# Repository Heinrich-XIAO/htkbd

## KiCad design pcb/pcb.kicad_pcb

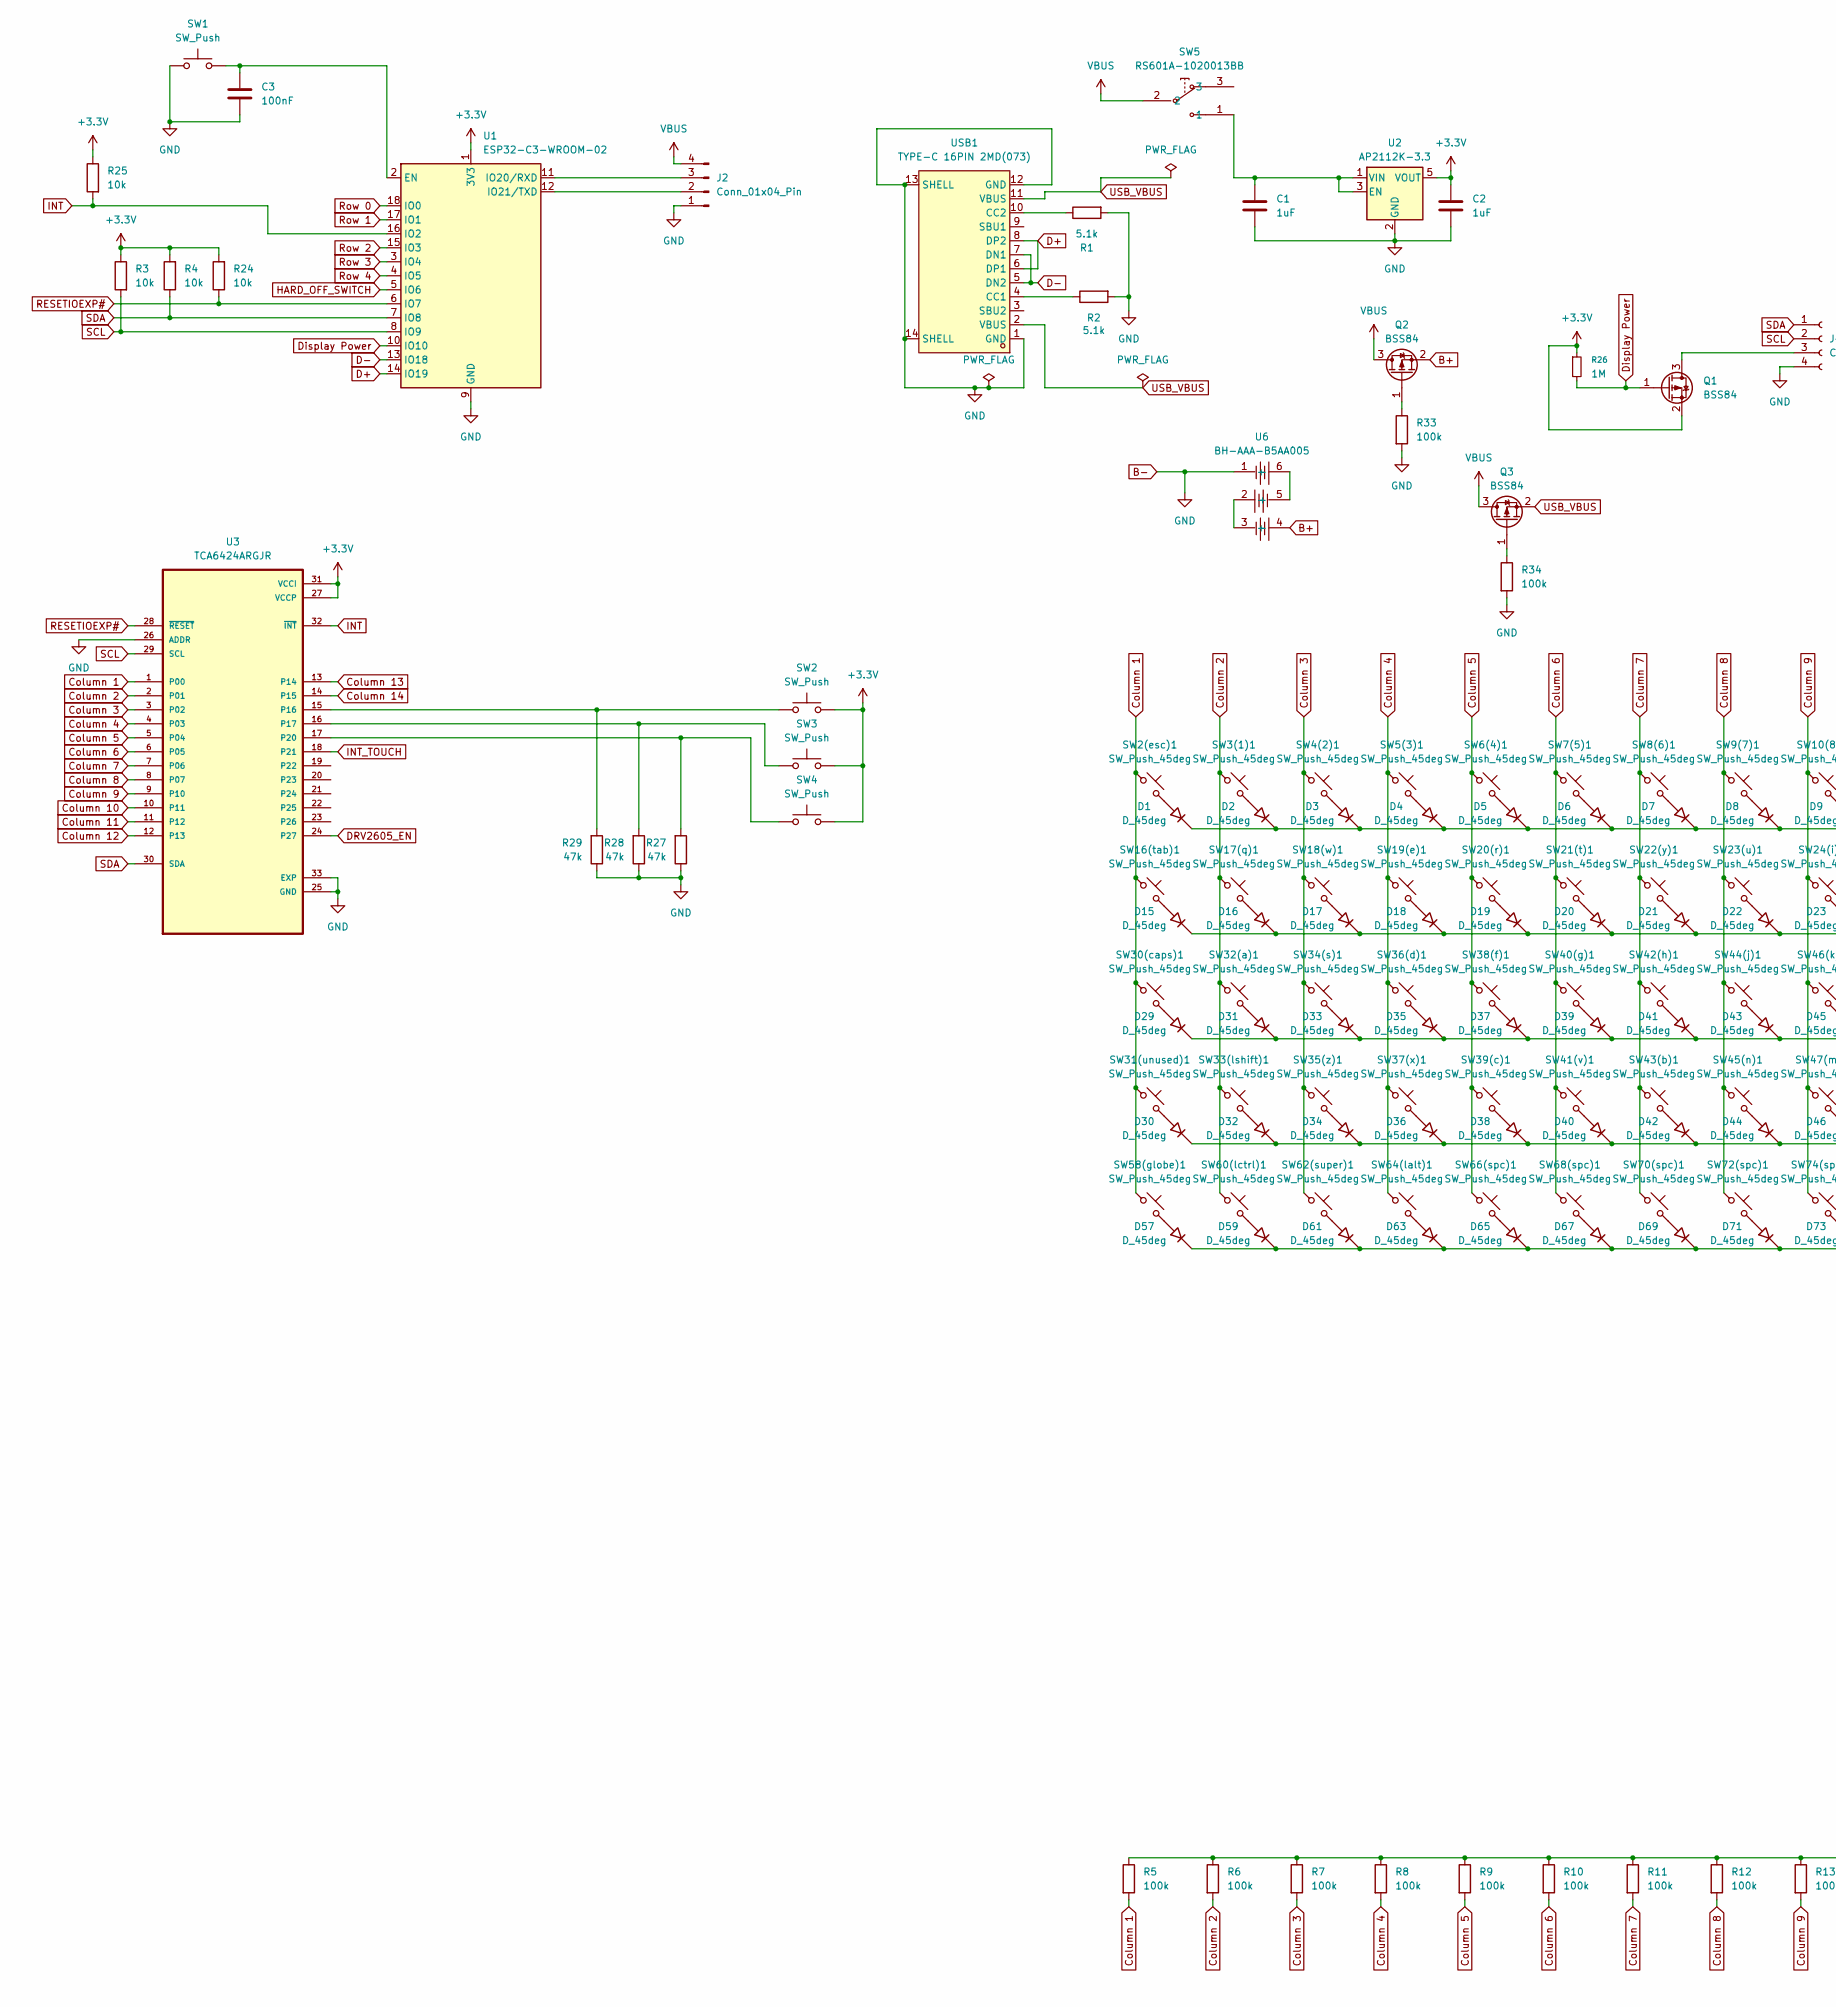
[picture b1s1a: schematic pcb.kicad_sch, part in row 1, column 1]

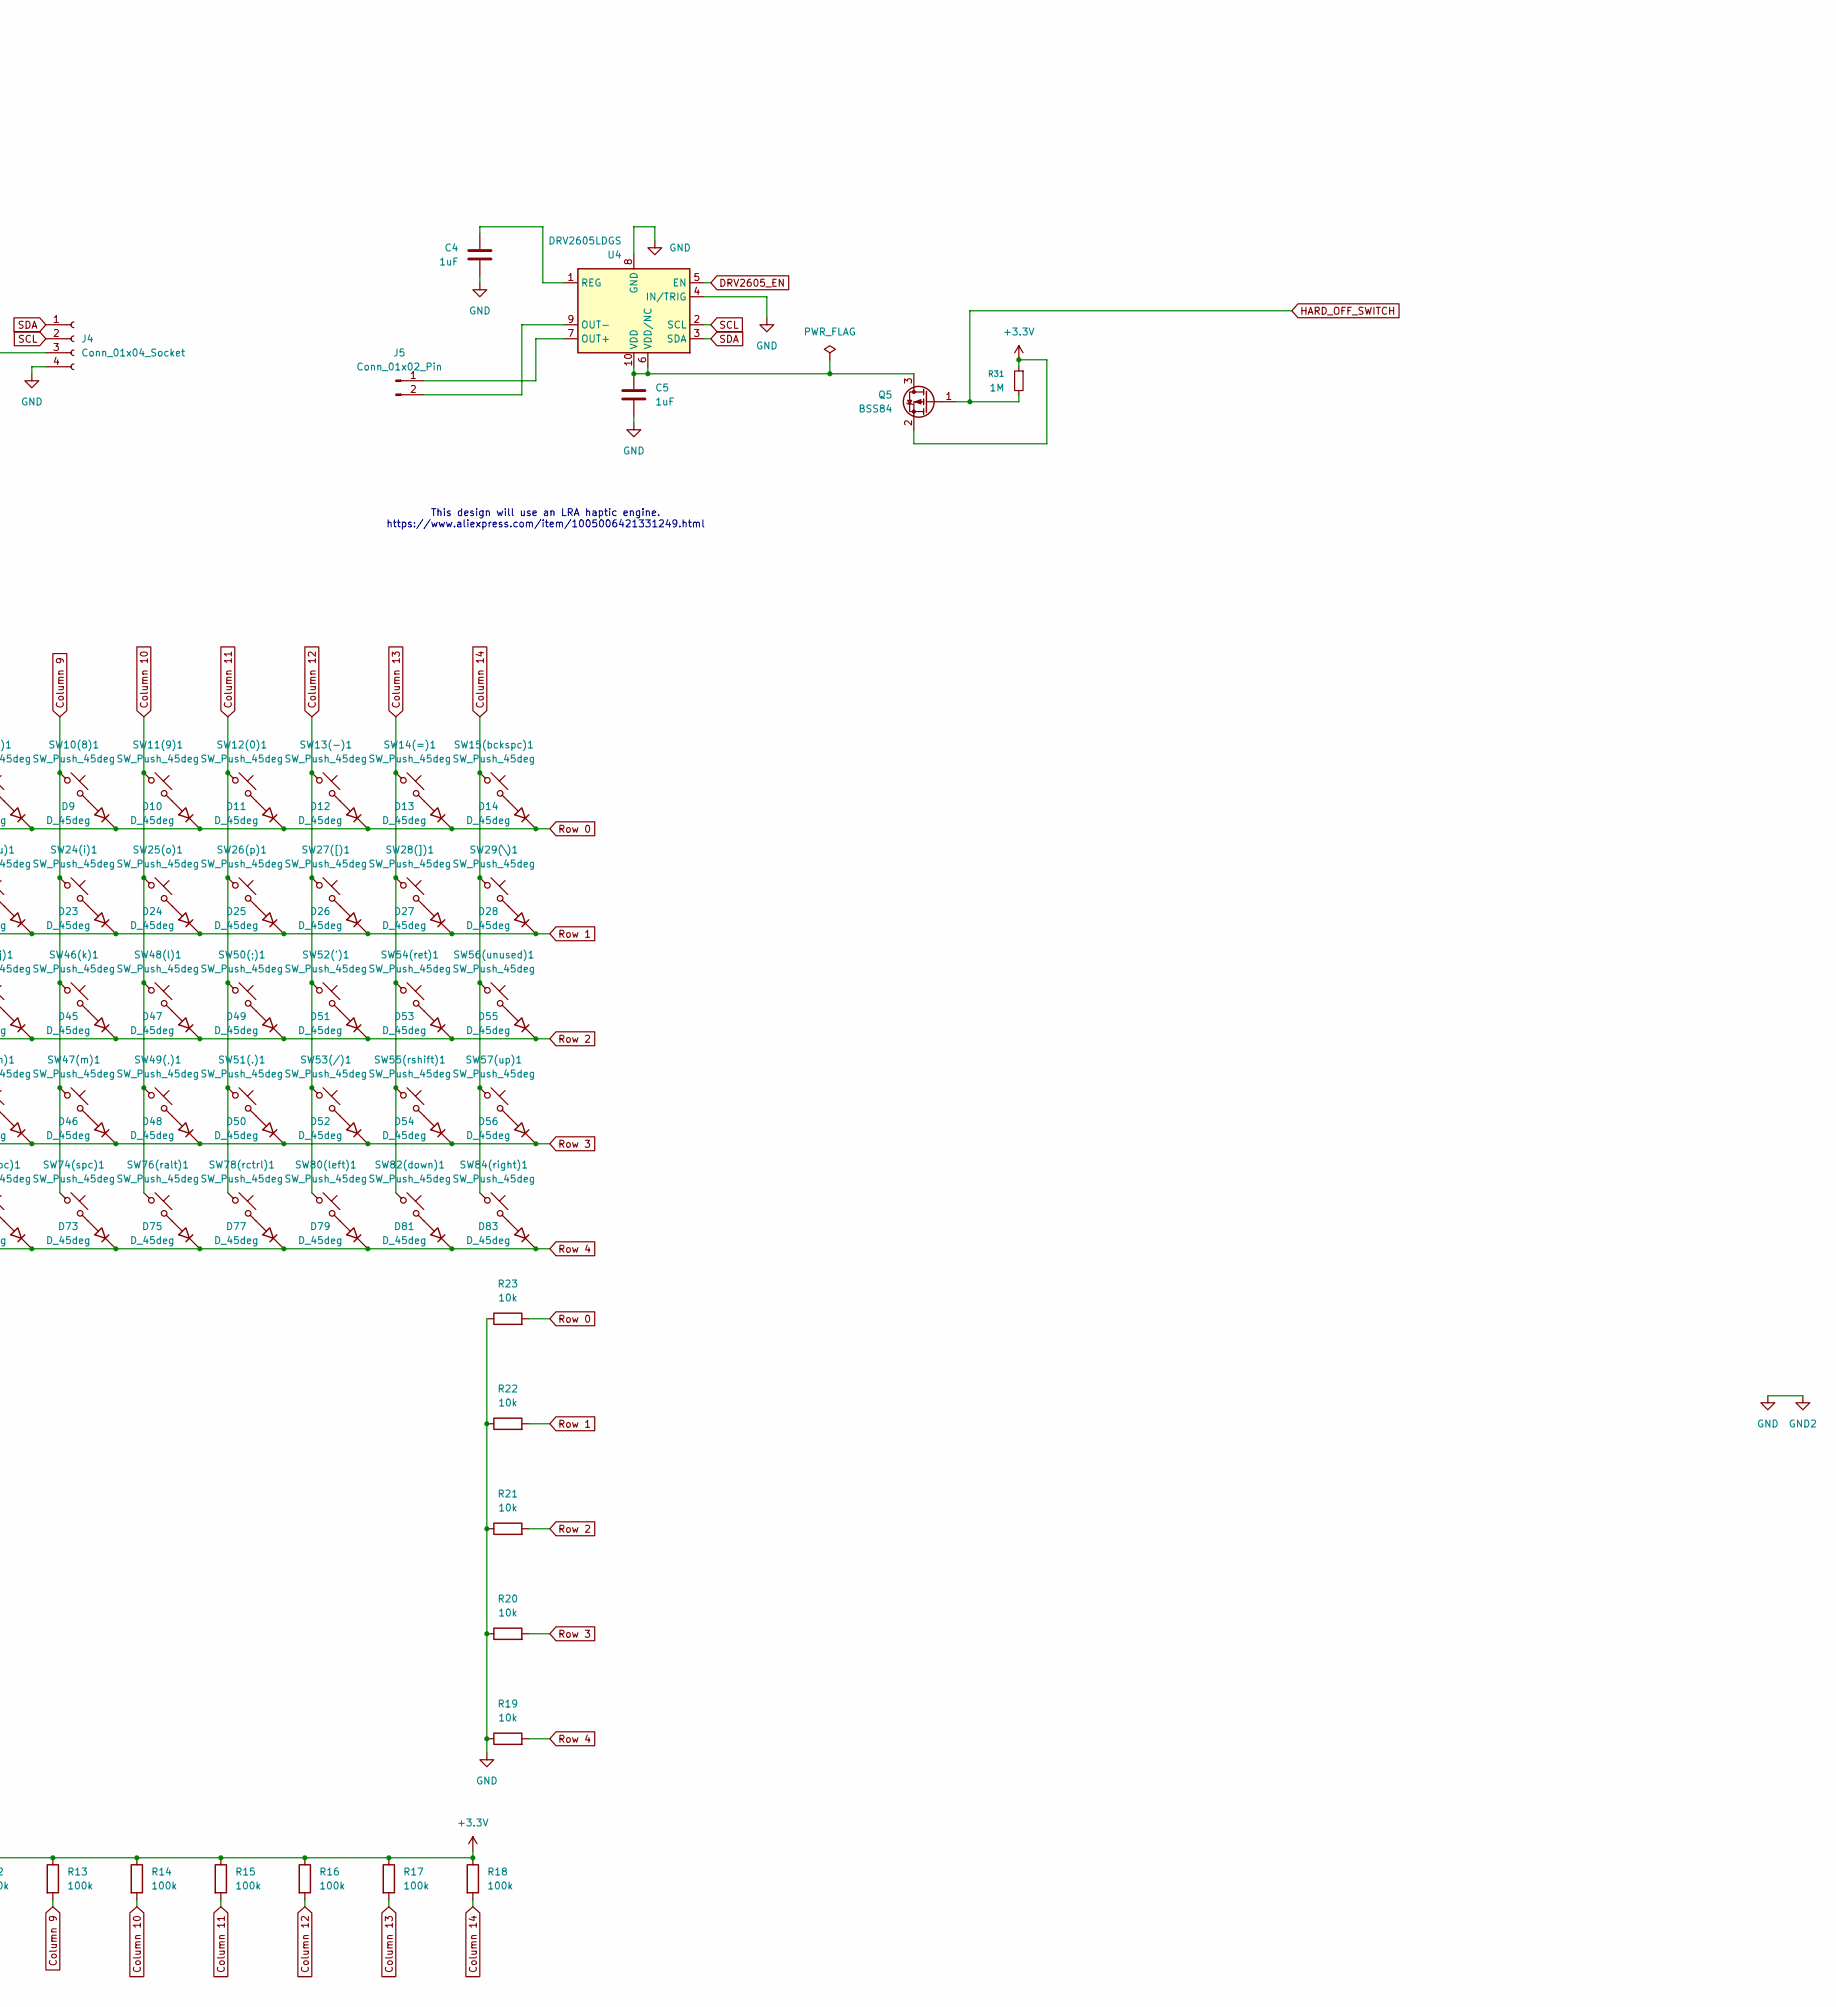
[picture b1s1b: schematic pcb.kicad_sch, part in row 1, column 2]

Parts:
C1, C2, C4, C5: 1uF; C_0603_1608Metric_Pad1.08x0.95mm_HandSolder
C3: 100nF; C_0603_1608Metric_Pad1.08x0.95mm_HandSolder
D1, D2, D3, D4, D5, D6, D7, D8, D9, D10, D11, D12, D13, D14, D15, D16, D17, D18, D19, D20, D21, D22, D23, D24, D25, D26, D27, D28, D29, D30, D31, D32, D33, D34, D35, D36, D37, D38, D39, D40, D41, D42, D43, D44, D45, D46, D47, D48, D49, D50, D51, D52, D53, D54, D55, D56, D57, D59, D61, D63, D65, D67, D69, D71, D73, D75, D77, D79, D81, D83: D_45deg; D_SOD-523
J2: Conn_01x04_Pin; PinHeader_1x04_P2.54mm_Vertical
J4: Conn_01x04_Socket; PinHeader_1x04_P2.54mm_Vertical
J5: Conn_01x02_Pin; PinHeader_1x02_P2.54mm_Vertical
Q1, Q2, Q3, Q5: BSS84; SOT-23
R1, R2: 5.1k; R_0603_1608Metric
R3, R4, R19, R20, R21, R22, R23, R24, R25: 10k; R_0805_2012Metric
R5, R6, R7, R8, R9, R10, R11, R12, R13, R14, R15, R16, R17, R18, R33, R34: 100k; R_1206_3216Metric_Pad1.30x1.75mm_HandSolder
R26, R31: 1M; R_1206_3216Metric_Pad1.30x1.75mm_HandSolder
R27, R28, R29: 47k; R_0402_1005Metric
SW1, SW2, SW3, SW4: SW_Push; SW_PUSH_6mm
SW2(esc)1, SW3(1)1, SW4(2)1, SW5(3)1, SW6(4)1, SW7(5)1, SW8(6)1, SW9(7)1, SW10(8)1, SW11(9)1, SW12(0)1, SW13(-)1, SW14(=)1, SW15(bckspc)1, SW16(tab)1, SW17(q)1, SW18(w)1, SW19(e)1, SW20(r)1, SW21(t)1, SW22(y)1, SW23(u)1, SW24(i)1, SW25(o)1, SW26(p)1, SW27([)1, SW28(])1, SW29(\)1, SW30(caps)1, SW31(unused)1, SW32(a)1, SW33(lshift)1, SW34(s)1, SW35(z)1, SW36(d)1, SW37(x)1, SW38(f)1, SW39(c)1, SW40(g)1, SW41(v)1, SW42(h)1, SW43(b)1, SW44(j)1, SW45(n)1, SW46(k)1, SW47(m)1, SW48(l)1, SW49(,)1, SW50(;)1, SW51(.)1, SW52(')1, SW53(/)1, SW54(ret)1, SW55(rshift)1, SW56(unused)1, SW57(up)1, SW58(globe)1, SW60(lctrl)1, SW62(super)1, SW64(lalt)1, SW66(spc)1, SW68(spc)1, SW70(spc)1, SW72(spc)1, SW74(spc)1, SW76(ralt)1, SW78(rctrl)1, SW80(left)1, SW82(down)1, SW84(right)1: SW_Push_45deg; Cherry_ULP_TH
SW5: RS601A-1020013BB; SW-TH_RS601A-1020013BB; LCSC Part C5124216
U1: ESP32-C3-WROOM-02
U2: AP2112K-3.3; SOT-23-5
U3: TCA6424ARGJR; QFN50P500X500X60-33N
U4: DRV2605LDGS; VSSOP-10_3x3mm_P0.5mm
U6: BH-AAA-B5AA005; LCSC Part C2979170
USB1: TYPE-C 16PIN 2MD(073); USB-C-SMD_TYPE-C-6PIN-2MD-073; LCSC Part C2765186

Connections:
+3.3V: C2.1, Q1.2 (S), Q5.2 (S), R3.1, R4.2, R5.1, R6.1, R7.1, R8.1, R9.1, R10.1, R11.1, R12.1, R13.1, R14.1, R15.1, R16.1, R17.1, R18.1, R24.2, R25.1, R26.1, R31.1, SW2.2, SW3.2, SW4.2, U1.1 (3V3), U2.5 (VOUT), U3.27 (VCCP), U3.31 (VCCI); also elsewhere on the board
B+: Q2.2 (S), U6.4 (+)
B-: C1.2, C2.2, C3.2, C4.2, C5.2, J2.1, J4.4, R1.2, R2.2, R19.1, R20.1, R21.1, R22.1, R23.1, R27.1, R28.1, R29.1, R33.2, R34.2, SW1.1, U1.9 (GND), U1.19 (GND), U2.2 (GND), U3.25 (GND), U3.26 (ADDR), U3.33 (EXP), U4.4 (IN/TRIG), U4.8 (GND), U6.1 (-), USB1.1 (GND), USB1.12 (GND), USB1.13 (SHELL), USB1.14 (SHELL); also elsewhere on the board
Column 1: R5.2, SW2(esc)1.1, SW16(tab)1.1, SW30(caps)1.1, SW31(unused)1.1, SW58(globe)1.1, U3.1 (P00)
Column 2: R6.2, SW3(1)1.1, SW17(q)1.1, SW32(a)1.1, SW33(lshift)1.1, SW60(lctrl)1.1, U3.2 (P01)
Column 3: R7.2, SW4(2)1.1, SW18(w)1.1, SW34(s)1.1, SW35(z)1.1, SW62(super)1.1, U3.3 (P02)
Column 4: R8.2, SW5(3)1.1, SW19(e)1.1, SW36(d)1.1, SW37(x)1.1, SW64(lalt)1.1, U3.4 (P03)
Column 5: R9.2, SW6(4)1.1, SW20(r)1.1, SW38(f)1.1, SW39(c)1.1, SW66(spc)1.1, U3.5 (P04)
Column 6: R10.2, SW7(5)1.1, SW21(t)1.1, SW40(g)1.1, SW41(v)1.1, SW68(spc)1.1, U3.6 (P05)
Column 7: R11.2, SW8(6)1.1, SW22(y)1.1, SW42(h)1.1, SW43(b)1.1, SW70(spc)1.1, U3.7 (P06)
Column 8: R12.2, SW9(7)1.1, SW23(u)1.1, SW44(j)1.1, SW45(n)1.1, SW72(spc)1.1, U3.8 (P07)
Column 9: R13.2, SW10(8)1.1, SW24(i)1.1, SW46(k)1.1, SW47(m)1.1, SW74(spc)1.1, U3.9 (P10)
Column 10: R14.2, SW11(9)1.1, SW25(o)1.1, SW48(l)1.1, SW49(,)1.1, SW76(ralt)1.1, U3.10 (P11)
Column 11: R15.2, SW12(0)1.1, SW26(p)1.1, SW50(;)1.1, SW51(.)1.1, SW78(rctrl)1.1, U3.11 (P12)
Column 12: R16.2, SW13(-)1.1, SW27([)1.1, SW52(')1.1, SW53(/)1.1, SW80(left)1.1, U3.12 (P13)
Column 13: R17.2, SW14(=)1.1, SW28(])1.1, SW54(ret)1.1, SW55(rshift)1.1, SW82(down)1.1, U3.13 (P14)
Column 14: R18.2, SW15(bckspc)1.1, SW29(\)1.1, SW56(unused)1.1, SW57(up)1.1, SW84(right)1.1, U3.14 (P15)
D+: U1.14 (IO19), USB1.6 (DP1), USB1.8 (DP2)
D-: U1.13 (IO18), USB1.5 (DN2), USB1.7 (DN1)
DRV2605_EN: U3.24 (P27), U4.5 (EN)
Display Power: Q1.1 (G), R26.2, U1.10 (IO10)
HARD_OFF_SWITCH: Q5.1 (G), R31.2, U1.5 (IO6)
INT: R25.2, U1.16 (IO2), U3.32 (~INT)
INT_TOUCH: U3.18 (P21)
unnamed: D1.2 (A), SW2(esc)1.2
unnamed: D2.2 (A), SW3(1)1.2
unnamed: D3.2 (A), SW4(2)1.2
unnamed: D4.2 (A), SW5(3)1.2
unnamed: D5.2 (A), SW6(4)1.2
unnamed: D6.2 (A), SW7(5)1.2
unnamed: D7.2 (A), SW8(6)1.2
unnamed: D8.2 (A), SW9(7)1.2
unnamed: D9.2 (A), SW10(8)1.2
unnamed: D10.2 (A), SW11(9)1.2
unnamed: D11.2 (A), SW12(0)1.2
unnamed: D12.2 (A), SW13(-)1.2
unnamed: D13.2 (A), SW14(=)1.2
unnamed: D14.2 (A), SW15(bckspc)1.2
unnamed: D15.2 (A), SW16(tab)1.2
unnamed: D16.2 (A), SW17(q)1.2
unnamed: D17.2 (A), SW18(w)1.2
unnamed: D18.2 (A), SW19(e)1.2
unnamed: D19.2 (A), SW20(r)1.2
unnamed: D20.2 (A), SW21(t)1.2
unnamed: D21.2 (A), SW22(y)1.2
unnamed: D22.2 (A), SW23(u)1.2
unnamed: D23.2 (A), SW24(i)1.2
unnamed: D24.2 (A), SW25(o)1.2
unnamed: D25.2 (A), SW26(p)1.2
unnamed: D26.2 (A), SW27([)1.2
unnamed: D27.2 (A), SW28(])1.2
unnamed: D28.2 (A), SW29(\)1.2
unnamed: D29.2 (A), SW30(caps)1.2
unnamed: D30.2 (A), SW31(unused)1.2
unnamed: D31.2 (A), SW32(a)1.2
unnamed: D32.2 (A), SW33(lshift)1.2
unnamed: D33.2 (A), SW34(s)1.2
unnamed: D34.2 (A), SW35(z)1.2
unnamed: D35.2 (A), SW36(d)1.2
unnamed: D36.2 (A), SW37(x)1.2
unnamed: D37.2 (A), SW38(f)1.2
unnamed: D38.2 (A), SW39(c)1.2
unnamed: D39.2 (A), SW40(g)1.2
unnamed: D40.2 (A), SW41(v)1.2
unnamed: D41.2 (A), SW42(h)1.2
unnamed: D42.2 (A), SW43(b)1.2
unnamed: D43.2 (A), SW44(j)1.2
unnamed: D44.2 (A), SW45(n)1.2
unnamed: D45.2 (A), SW46(k)1.2
unnamed: D46.2 (A), SW47(m)1.2
unnamed: D47.2 (A), SW48(l)1.2
unnamed: D48.2 (A), SW49(,)1.2
unnamed: D49.2 (A), SW50(;)1.2
unnamed: D50.2 (A), SW51(.)1.2
unnamed: D51.2 (A), SW52(')1.2
unnamed: D52.2 (A), SW53(/)1.2
unnamed: D53.2 (A), SW54(ret)1.2
unnamed: D54.2 (A), SW55(rshift)1.2
unnamed: D55.2 (A), SW56(unused)1.2
unnamed: D56.2 (A), SW57(up)1.2
unnamed: D57.2 (A), SW58(globe)1.2
unnamed: D59.2 (A), SW60(lctrl)1.2
unnamed: D61.2 (A), SW62(super)1.2
unnamed: D63.2 (A), SW64(lalt)1.2
unnamed: D65.2 (A), SW66(spc)1.2
unnamed: D67.2 (A), SW68(spc)1.2
unnamed: D69.2 (A), SW70(spc)1.2
unnamed: D71.2 (A), SW72(spc)1.2
unnamed: D73.2 (A), SW74(spc)1.2
unnamed: D75.2 (A), SW76(ralt)1.2
unnamed: D77.2 (A), SW78(rctrl)1.2
unnamed: D79.2 (A), SW80(left)1.2
unnamed: D81.2 (A), SW82(down)1.2
unnamed: D83.2 (A), SW84(right)1.2
unnamed: J2.2, U1.12 (IO21/TXD)
unnamed: J2.3, U1.11 (IO20/RXD)
unnamed: J4.3, Q1.3 (D)
unnamed: J5.1, U4.7 (OUT+)
unnamed: J5.2, U4.9 (OUT-)
unnamed: Q2.1 (G), R33.1
unnamed: Q3.1 (G), R34.1
unnamed: C5.1, Q5.3 (D), U4.6 (VDD/NC), U4.10 (VDD)
unnamed: C3.1, SW1.2, U1.2 (EN)
unnamed 105: C1.1, SW5.1, U2.1 (VIN), U2.3 (EN); also elsewhere on the board
unnamed: R29.2, SW2.1, U3.15 (P16)
unnamed: R28.2, SW3.1, U3.16 (P17)
unnamed: R27.2, SW4.1, U3.17 (P20)
unnamed: C4.1, U4.1 (REG)
unnamed: U6.2 (+), U6.3 (-)
unnamed: U6.5 (-), U6.6 (+)
unnamed: R2.1, USB1.4 (CC1)
unnamed: R1.1, USB1.10 (CC2)
RESETIOEXP#: R24.1, U1.6 (IO7), U3.28 (~RESET)
Row 0: D1.1 (K), D2.1 (K), D3.1 (K), D4.1 (K), D5.1 (K), D6.1 (K), D7.1 (K), D8.1 (K), D9.1 (K), D10.1 (K), D11.1 (K), D12.1 (K), D13.1 (K), D14.1 (K), R23.2, U1.18 (IO0)
Row 1: D15.1 (K), D16.1 (K), D17.1 (K), D18.1 (K), D19.1 (K), D20.1 (K), D21.1 (K), D22.1 (K), D23.1 (K), D24.1 (K), D25.1 (K), D26.1 (K), D27.1 (K), D28.1 (K), R22.2, U1.17 (IO1)
Row 2: D29.1 (K), D31.1 (K), D33.1 (K), D35.1 (K), D37.1 (K), D39.1 (K), D41.1 (K), D43.1 (K), D45.1 (K), D47.1 (K), D49.1 (K), D51.1 (K), D53.1 (K), D55.1 (K), R21.2, U1.15 (IO3)
Row 3: D30.1 (K), D32.1 (K), D34.1 (K), D36.1 (K), D38.1 (K), D40.1 (K), D42.1 (K), D44.1 (K), D46.1 (K), D48.1 (K), D50.1 (K), D52.1 (K), D54.1 (K), D56.1 (K), R20.2, U1.3 (IO4)
Row 4: D57.1 (K), D59.1 (K), D61.1 (K), D63.1 (K), D65.1 (K), D67.1 (K), D69.1 (K), D71.1 (K), D73.1 (K), D75.1 (K), D77.1 (K), D79.1 (K), D81.1 (K), D83.1 (K), R19.2, U1.4 (IO5)
SCL: J4.2, R3.2, U1.8 (IO9), U3.29 (SCL), U4.2 (SCL); also elsewhere on the board
SDA: J4.1, R4.1, U1.7 (IO8), U3.30 (SDA), U4.3 (SDA); also elsewhere on the board
USB_VBUS: Q3.2 (S), USB1.2 (VBUS), USB1.11 (VBUS)
VBUS: J2.4, Q2.3 (D), Q3.3 (D), SW5.2

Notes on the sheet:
This design will use an LRA haptic engine. https://www.aliexpress.com/item/1005006421331249.html

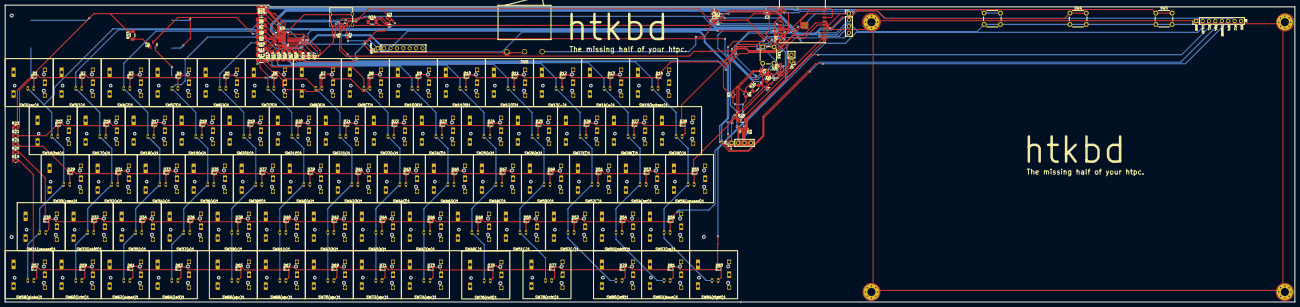
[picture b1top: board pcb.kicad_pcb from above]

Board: 2 copper layers, 511.6 x 117.8 mm, 200 parts (1 on the bottom side), 122 nets.

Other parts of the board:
H1, H2, H3, H4: MountingHole_Pad; MountingHole_3.2mm_M3_Pad_Via
J8: Conn_01x08_Pin; PinHeader_1x08_P2.54mm_Vertical

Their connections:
+3.3V: J8.2; also elsewhere on the board
B-: H1.1, H2.1, H3.1, H4.1, J8.1; also elsewhere on the board
GND2: H1.1, H2.1, H3.1, H4.1
unnamed 105: J8.7; also elsewhere on the board
SCL: J8.3; also elsewhere on the board
SDA: J8.4; also elsewhere on the board

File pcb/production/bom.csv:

Designator,Footprint,Quantity,Value,LCSC Part #
"C1, C2, C4, C5",0603,4,1uF,
C3,0603,1,100nF,
"D1, D10, D11, D12, D13, D14, D15, D16, D17, D18, D19, D2, D20, D21, D22, D23, D24, D25, D26, D27, D28, D29, D3, D30, D31, D32, D33, D34, D35, D36, D37, D38, D39, D4, D40, D41, D42, D43, D44, D45, D46, D47, D48, D49, D5, D50, D51, D52, D53, D54, D55, D56, D57, D59, D6, D61, D63, D65, D67, D69, D7, D71, D73, D75, D77, D79, D8, D81, D83, D9",D_SOD-523,70,D_45deg,
J2,PinHeader_1x04_P2.54mm_Vertical,1,Conn_01x04_Pin,
J4,PinHeader_1x04_P2.54mm_Vertical,1,Conn_01x04_Socket,
J5,PinHeader_1x02_P2.54mm_Vertical,1,Conn_01x02_Pin,
"Q1, Q2, Q3, Q5",SOT-23,4,BSS84,
"R1, R2",0603,2,5.1k,
"R10, R11, R12, R13, R14, R15, R16, R17, R18, R33, R34, R5, R6, R7, R8, R9",1206,16,100k,
"R19, R20, R21, R22, R23, R24, R25, R3, R4",0805,9,10k,
"R26, R31",1206,2,1M,
"R27, R28, R29",0402,3,47k,
"SW1, SW2, SW3, SW4",SW_PUSH_6mm,4,SW_Push,
"SW10(8)1, SW11(9)1, SW12(0)1, SW13(-)1, SW14(=)1, SW15(BCKSPC)1, SW16(TAB)1, SW17(Q)1, SW18(W)1, SW19(E)1, SW2(ESC)1, SW20(R)1, SW21(T)1, SW22(Y)1, SW23(U)1, SW24(I)1, SW25(O)1, SW26(P)1, SW27([)1, SW28(])1, SW29(\)1, SW3(1)1, SW30(CAPS)1, SW31(UNUSED)1, SW32(A)1, SW33(LSHIFT)1, SW34(S)1, SW35(Z)1, SW36(D)1, SW37(X)1, SW38(F)1, SW39(C)1, SW4(2)1, SW40(G)1, SW41(V)1, SW42(H)1, SW43(B)1, SW44(J)1, SW45(N)1, SW46(K)1, SW47(M)1, SW48(L)1, SW49(,)1, SW5(3)1, SW50(;)1, SW51(.)1, SW52(')1, SW53(/)1, SW54(RET)1, SW55(RSHIFT)1, SW56(UNUSED)1, SW57(UP)1, SW58(GLOBE)1, SW6(4)1, SW60(LCTRL)1, SW62(SUPER)1, SW64(LALT)1, SW66(SPC)1, SW68(SPC)1, SW7(5)1, SW70(SPC)1, SW72(SPC)1, SW74(SPC)1, SW76(RALT)1, SW78(RCTRL)1, SW8(6)1, SW80(LEFT)1, SW82(DOWN)1, SW84(RIGHT)1, SW9(7)1",Cherry_ULP_TH,70,SW_Push_45deg,
SW5,SW-TH_RS601A-1020013BB,1,RS601A-1020013BB,C5124216
U1,ESP32-C3-WROOM-02,1,ESP32-C3-WROOM-02,
U2,SOT-23-5,1,AP2112K-3.3,
U3,QFN50P500X500X60-33N,1,TCA6424ARGJR,
U4,VSSOP-10_3x3mm_P0.5mm,1,DRV2605LDGS,
U6,BH-AAA-B5AA005,1,BH-AAA-B5AA005,C2979170
USB1,USB-C-SMD_TYPE-C-6PIN-2MD-073,1,TYPE-C 16PIN 2MD(073),C2765186

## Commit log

2025-08-05 Rename README to README.md
2025-08-10 lock in and get most of the kbd done
2025-08-12 make own symbol for touch ic because others sucked ass
2025-08-12 add nc flag to nc pins on symbol and most importantly, connect all the necessary components to get the touchic funcitoning (ATMXT1664T3-CCUR035 136-ball bga version)
2025-08-12 remove lock files
2025-08-12 add all of the footprints
2025-08-14 arrange components for touch ic, and all keys:
2025-08-15 trackpad connected to touch ic. not fully though. i accidentally connected the x to the columns and y to the rows, so i fucked that up and now have to just suck it up. yay! the width of the trackpad 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
2025-08-17 add stuff
2025-08-17 add edge cuts
2025-08-17 add branding
2025-08-18 stuff
2025-08-19 remove entire trackpad and replace with attatchement for hat (modified from the peacock)
2025-08-20 make a hat attatchement
